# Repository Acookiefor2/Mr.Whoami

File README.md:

# Mr. Whoami?

A little desk buddy with a face. You chat with it, and you have to figure out one thing:

**Is it a dumb hardcoded script... or an AI *pretending* to be a dumb hardcoded script?**

When you think you know, you slam one of two big buttons: **SCRIPT** or **AI**. Then it reveals the truth.

## 🤔 What even is THIS?
Mr. Whoami? is a lil guy ofc but also a physical version of my earlier project, [Script or AI?](https://github.com/Acookiefor2/script-or-ai). In that one, an AI was the interrogator: it questioned a hidden opponent and tried to guess whether it was a real script or an AI faking one.

This time, **YOU, the human, are the interrogator.**

Every round, Mr. Whoami secretly flips a coin (sneaky):
- **Heads:** you're talking to a real rule-based script.
- **Tails:** you're talking to a small AI model told to act exactly like that script.

You type questions, it answers with a face and little blip sounds, and you try to catch it out.

## 🎮 How a round works
1. Press **START**. The laptop secretly picks script or AI.
2. Type questions on the keyboard for ~90 seconds. Mr. Whoami answers on its screen.
3. Slam **SCRIPT** or **AI**.
4. Reveal!!! The face reacts, the buttons light up, and it plays a win or lose sound.
5. The crowd scoreboard updates (e.g. "humans fooled: 58%").

## 💡 Why build it?
Shenzhen is full of people who are way better at hardware than me. So instead of trying to out-engineer them and trying to beat them at their own game, I'm changing the battle ground by challenging them: **bet you can't tell.**

It's also a real experiment. By the end, I'll have data on how good **humans** are at this compared to the **AI interrogator** from my first project, at the exact same task. (which comparing humans to ai is always fun)

## ⚖️ Keeping it fair
If the script answered instantly and the AI took 2 seconds, anyone and their mother would win in one round. So:
- **Same delay:** every reply waits the same amount of time, shown as a "thinking" face.
- **Same voice:** no text-to-speech. Both modes use the same per-letter blip sounds (Animal Crossing style).
- **Same style:** the AI is prompted to match the script's tone, length and formatting.

## 🧠 How it works

```
 [ Keyboard ] --USB--> [ Mr. Whoami (ESP32-S3) ] <--USB cable--> [ Laptop "brain" ]
                         - 3.5" screen (face + chat)              - game logic
                         - SCRIPT / AI arcade buttons             - rule-based script
                         - START button                           - local AI model (Ollama)
                         - speaker (blips)                        - logging + scoreboard
                         - LED ring (reveal)                      - crowd stats on laptop screen
```

**Minor note: the AI does NOT run on the ESP32.** A microcontroller can't run a language model. Mr. Whoami is the body: face, buttons and sound. The brain is my laptop, running a small local model (Llama 3.2 3B or Qwen 2.5 3B through [Ollama](https://ollama.com)). (hopefully you didn't think that an local llm would run on like under 1 mb raam)

Why local and not a cloud API?
- Most Western AI APIs are blocked in China, so a cloud demo could die on the show floor.
- Expo Wi-Fi could be unreliable. One USB cable carries both power and data, so there's no Wi-Fi involved. 

## 🛠️ Hardware
| Part | What it does |
|---|---|
| ESP32-S3-DevKitC-1 (N16R8) | The microcontroller. Drives the screen, reads buttons and keyboard, plays sounds, talks to the laptop |
| 3.5" SPI TFT display (ST7796, 480x320) | The face on top, the chat underneath |
| 2x 60mm LED arcade buttons | SCRIPT and AI, made for slamming |
| Small push button | START / new round |
| MAX98357A I2S amp + 8Ω speaker | Blip voice and sound effects |
| WS2812B LED ring | Red/green reveal effect |
| Custom carrier PCB | Everything plugs into one board instead of a rat's nest of jumper wires |
| ABS project box | The body, cut and drilled by hand, then decorated |

Full parts list with prices: [`BOM.csv`](./BOM.csv).

### About the PCB
This is my first PCB, so it's deliberately simple: a **carrier board**. The DevKit and the modules plug into headers on it, and it routes the connections between them. No power circuitry, no tiny parts. If the PCB fails, the backup is the same circuit on perfboard.

### Enclosure
I modelled the whole thing in Onshape before buying anything so I could know EXACTLY where every hole goes and well the screen is on the front wall the SCRIPT/AI/START buttons are on the lid and the USB cables come out the right side. The model caught a problem early: the DevKit's USB ports were pointing straight into the back of the screen, so I had to like rotate the board 90° inside the box. (which was scary)

## 📸 Pictures

### Schematic

### PCB

### 3D view

### Enclosure

Onshape model: [open in Onshape](https://cad.onshape.com/documents/b74af73a844940a9566ad19c/w/d542cf5fa6340909a52c948a/e/57c35baeb29c6b37f6020392)

STEP files: [`CAD/Mr.Whoami-enclosure.step`](CAD/Mr.Whoami-enclosure.step) (full box) and [`CAD/Mr.Whoami.step`](CAD/Mr.Whoami.step) (PCB only)

## 📂 Repo structure
* `BOM.csv` - Parts list with prices and links.
* `/schematics` - KiCad schematic, carrier PCB and Gerbers.
* `/CAD` - STEP files for the PCB and the enclosure.
* `/images` - Pictures used in this README.
* `/firmware` - ESP32-S3 code: display, face animations, buttons, keyboard, sound.
* `/brain` - (I'll do this soon) Python on the laptop: script, local model, game logic, logging, scoreboard.

## 🗺️ Plan 
(small change to it)
| When | What |
|---|---|
| Nov 1 - 10 | Schematic, carrier PCB, BOM, enclosure model. Submit the design |
| Nov 11 - 17 | Order parts. Get the laptop brain working (script + local model + game loop) |
| Nov 18 - Dec 1 | Build: wire everything up, firmware, face animations, enclosure |
| Dec 2 - 9 | Playtest with real humans, fix tells, polish |
| Dec 11 | Finished and submitted |

## 🚧 Status
Schematic carrier PCB (DRC clean :D) Gerbers, BOM and the enclosure model are done,next are firmware sketch and then design submission.

## ⚠️ Known risks / open questions
- **Power:** the speaker, LEDs and screen together might pull more than a laptop USB port gives. A separate 5V USB charger is the fallback.
- **Keyboard:** the DevKit's second USB port has to act as a USB host and supply 5V to the keyboard. Still need to confirm the exact setup.
- **Speed:** a 3B model on a laptop CPU should take a few seconds per short reply. The fixed delay hides this, but it still has to be tested.
- **Button depth:** the arcade buttons' depth below the lid isn't listed anywhere on the website when checked so the model assumes 45mm which clears the board and I'll check it when they arrive

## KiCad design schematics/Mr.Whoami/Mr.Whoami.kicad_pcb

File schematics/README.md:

# Schematics & Wiring
Pinout diagrams and the breadboard wiring schematics and KiCad design files for Mr.Whoami will be uploaded here

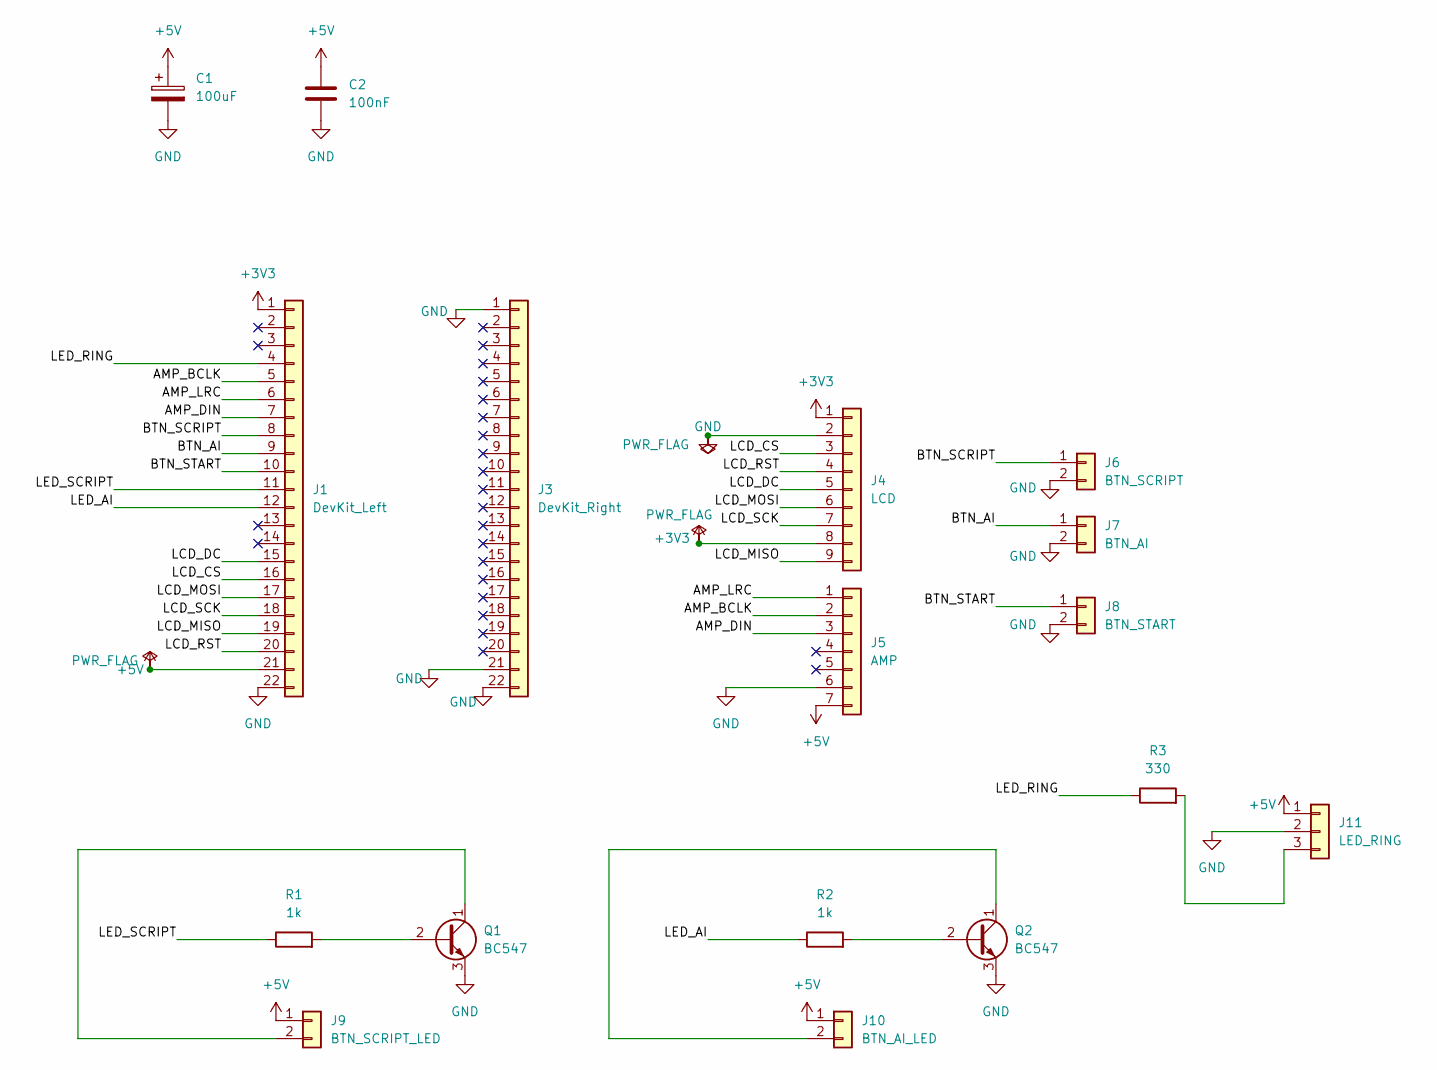
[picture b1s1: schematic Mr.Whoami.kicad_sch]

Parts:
C1: 100uF; CP_Radial_D6.3mm_P2.50mm
C2: 100nF; C_Disc_D5.0mm_W2.5mm_P5.00mm
J1: DevKit_Left; PinSocket_1x22_P2.54mm_Vertical
J3: DevKit_Right; PinSocket_1x22_P2.54mm_Vertical
J4: LCD; PinHeader_1x09_P2.54mm_Vertical
J5: AMP; PinSocket_1x07_P2.54mm_Vertical
J6: BTN_SCRIPT; PinHeader_1x02_P2.54mm_Vertical
J7: BTN_AI; PinHeader_1x02_P2.54mm_Vertical
J8: BTN_START; PinHeader_1x02_P2.54mm_Vertical
J9: BTN_SCRIPT_LED; PinHeader_1x02_P2.54mm_Vertical
J10: BTN_AI_LED; PinHeader_1x02_P2.54mm_Vertical
J11: LED_RING; PinHeader_1x03_P2.54mm_Vertical
Q1, Q2: BC547; TO-92_Inline
R1, R2: 1k; R_Axial_DIN0207_L6.3mm_D2.5mm_P10.16mm_Horizontal
R3: 330; R_Axial_DIN0207_L6.3mm_D2.5mm_P10.16mm_Horizontal

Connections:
+3V3: J1.1, J4.1, J4.8
+5V: C1.1, C2.1, J1.21, J5.7, J9.1, J10.1, J11.1
/AMP_BCLK: J1.5, J5.2
/AMP_DIN: J1.7, J5.3
/AMP_LRC: J1.6, J5.1
/BTN_AI: J1.9, J7.1
/BTN_SCRIPT: J1.8, J6.1
/BTN_START: J1.10, J8.1
/LCD_CS: J1.16, J4.3
/LCD_DC: J1.15, J4.5
/LCD_MISO: J1.19, J4.9
/LCD_MOSI: J1.17, J4.6
/LCD_RST: J1.20, J4.4
/LCD_SCK: J1.18, J4.7
/LED_AI: J1.12, R2.1
/LED_RING: J1.4, R3.1
/LED_SCRIPT: J1.11, R1.1
GND: C1.2, C2.2, J1.22, J3.1, J3.21, J3.22, J4.2, J5.6, J6.2, J7.2, J8.2, J11.2, Q1.3 (E), Q2.3 (E)
unnamed: J9.2, Q1.1 (C)
unnamed: J10.2, Q2.1 (C)
unnamed: J11.3, R3.2
unnamed: Q1.2 (B), R1.2
unnamed: Q2.2 (B), R2.2

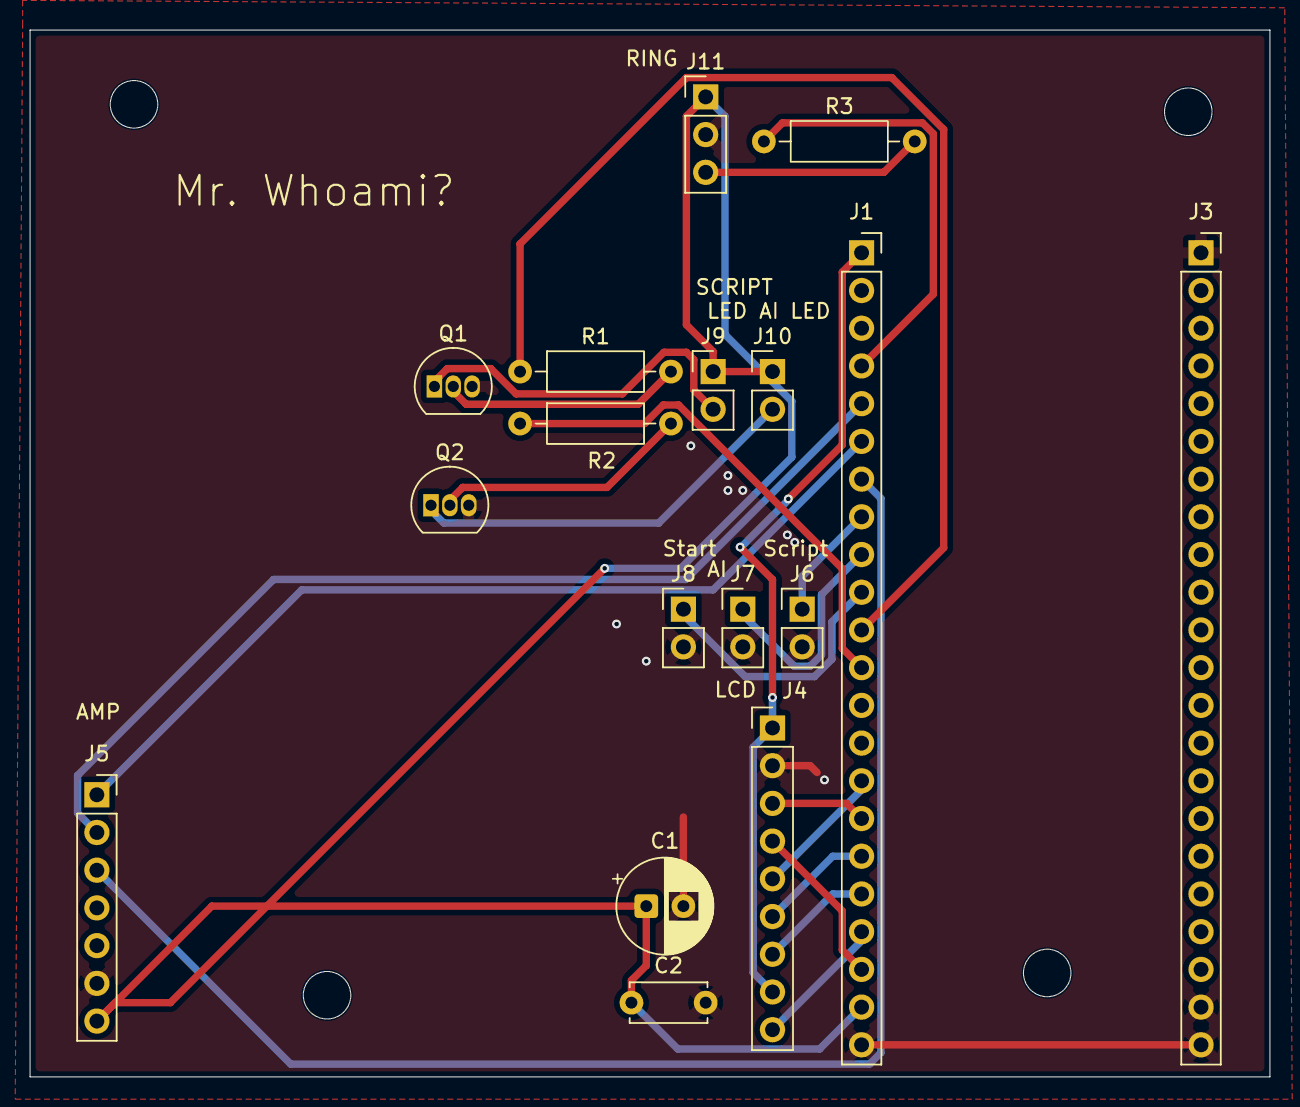
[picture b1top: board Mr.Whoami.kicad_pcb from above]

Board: 2 copper layers, 83.5 x 70.5 mm, 21 parts (0 on the bottom side), 23 nets.

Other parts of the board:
H1, H2, H3, H4: MountingHole_3.2mm_M3
